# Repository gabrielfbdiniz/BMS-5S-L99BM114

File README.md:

# BMS 5S (L99BM114) — Formula ITA
### Módulo Escravo Distribuído de Sensoriamento de Células, Balanceamento e Termistores NTC (Formula SAE EV)

Repositório oficial de **Hardware** e **Documentação Técnica** do módulo escravo (Slave) do Battery Management System (BMS) da equipe **Formula ITA** (Temporada 2025-2026).

---

## Renderizações 3D do Hardware

### Módulo BMS 5S Slave (L99BM114)

Placa de 4 camadas dedicada ao monitoramento de cada bloco 5S, dotada de barreira galvânica de isolação automotiva, balanceamento passivo e filtros diferenciais de alta precisão.

<div align="center">
  
  <p><em>Vista Isométrica Superior — Destaque para o ASIC ST L99BM114, transformadores de pulso Pulse HMU2103NL (Isolated SPI Daisy-Chain), filtros de entrada e conectores Molex Micro-Fit 3.0.</em></p>
</div>

<br>

| Perspectiva Superior (Iso Top) | Perspectiva Inferior (Iso Bottom) |
| :---: | :---: |
|  |  |
| **Vista Ortográfica Superior (Top View)** | **Vista Ortográfica Inferior (Bottom View)** |
|  |  |

---

## Destaques de Arquitetura e Engenharia

1. **Topologia do Sistema no Acumulador:**
   * O acumulador total de tração é composto por **8 módulos 5s18p** em série (**40S18P = 720 células** formato 21700, 168V nominais).
   * Cada módulo possui **1x Placa BMS 5S Slave**, comunicando-se em cadeia (daisy-chain) com o BMS Master.
2. **ASIC Automotivo de Alta Resolução (ST L99BM114):**
   * Medição síncrona de tensão de células com ADC de 16 bits ($\pm 1{,}5\text{ mV}$).
   * Balanceamento passivo programável por PWM individual com resistores de potência no layer inferior.
3. **Sensoriamento Térmico Abrangente (FSAE EV4.4):**
   * Interface multiplexada para leitura de termistores NTC 10k 1% por módulo, atendendo aos requisitos de amostragem térmica de células do regulamento FSAE.
4. **Proteção Intrínseca e Filtragem EMI (FSAE EV4.4):**
   * Linhas de medição de tensão protegidas por resistores limitadores de corrente série (`R8, R11, R12, R15, R16` de 100 $\Omega$, 0805) e Ferrite Beads `TDK MMZ2012S102AT000` (1 k$\Omega$ @ 100 MHz, 0805), limitando correntes de curto-circuito em conformidade com o regulamento e atenuando transientes EMI do inversor trifásico.
   * Diodo TVS automotivo `SMA6T68AY` e capacitores cerâmicos de desacoplamento ESD (100 nF / 100 V X7R) em todas as entradas de sensoriamento.
5. **Comunicação Segura em Daisy-Chain (FSAE EV4.8 / IEC 60664):**
   * Barramento Iso-SPI diferencial serial acoplado via transformadores `Pulse HMU2103NL` ($\ge 2500\text{ V}_{RMS}$, creepage $\ge 4{,}0\text{ mm}$ e folga no layout $\ge 6{,}5\text{ mm}$).

---

## Mapeamento de Pinos do Conector de Sensoriamento (J3)

O conector **J3** (Molex Micro-Fit 3.0 de 16 vias — `43045-1600`) é a interface primária do BMS Slave para leitura das tensões de célula, linhas Kelvin de corrente e termistores NTC multiplexados:

| Pino J3 | Sinal | Descrição Técnica |
|:---:|:---:|:---|
| **1** | `BATT14` | Tensão Célula 5 (Topo do módulo, até 21.0V) — Mapeado em Cell 14 do L99BM114 |
| **2** | `BATT13` | Tensão Célula 4 (Até 16.8V) — Mapeado em Cell 13 do L99BM114 |
| **3** | `BATT12` | Tensão Célula 3 (Até 12.6V) — Mapeado em Cell 12 do L99BM114 |
| **4** | `BATT2`  | Tensão Célula 2 (Até 8.4V) — Mapeado em Cell 2 do L99BM114 |
| **5** | `BATT1`  | Tensão Célula 1 (Até 4.2V) — Mapeado em Cell 1 do L99BM114 |
| **6** | `GND_ESD`| Retorno / Referência Negativa do Módulo (0V local) |
| **7** | `ISENSEM_conn` | Entrada Kelvin negativa de sensoriamento de corrente (remoto) |
| **8** | `ISENSEP_conn` | Entrada Kelvin positiva de sensoriamento de corrente (remoto) |
| **9** | `MUX_S2` | Linha de controle digital: Bit 2 dos multiplexadores de NTC |
| **10**| `MUX_S1` | Linha de controle digital: Bit 1 dos multiplexadores de NTC |
| **11**| `MUX_S0` | Linha de controle digital: Bit 0 dos multiplexadores de NTC |
| **12**| `AGND`   | Referência analógica de sensoriamento NTC |
| **13**| `NTC_CH4`| Canal analógico multiplexado 4 (NTCs 25 a 32) |
| **14**| `NTC_CH3`| Canal analógico multiplexado 3 (NTCs 17 a 24) |
| **15**| `NTC_CH2`| Canal analógico multiplexado 2 (NTCs 9 a 16) |
| **16**| `NTC_CH1`| Canal analógico multiplexado 1 (NTCs 1 a 8) |

---

## Topologia de Células, Balanceamento e Componentes DNP (Do Not Populate)

### Topologia 5S no L99BM114
O L99BM114 é um AFE automotivo configurável de 4 a 14 células em série. Conforme a Seção 6.8 do datasheet da STMicroelectronics, as células externas (`Cell 1, 2, 13 e 14`) são mandatórias. Na topologia 5S deste projeto:
- **Células Ativas Monitoradas e Balanceadas:** `Cell 1`, `Cell 2`, `Cell 12`, `Cell 13` e `Cell 14`.
- **Células Não Utilizadas (Cell 3 a 11):** Os pinos de entrada analógica correspondentes estão interligados internamente ao barramento `/NC2` (pinos 32 a 50) e acoplados a `B2_1` através do resistor `R5 (1 kΩ)`, garantindo estabilidade do conversor ADC e impedindo nós flutuantes.

### Tabela de Componentes DNP (NÃO MONTAR)
Os seguintes componentes estão definidos formalmente como **DNP** na montagem:
| Componente | Função Original | Motivo do DNP no Módulo Slave |
| :---: | :---: | :--- |
| **`R17`** (39 $\Omega$, 2010) | Balanceamento de Cell 11 (`S11`) | Canal de célula inexistente na topologia 5S. Não montar para evitar polarização indevida do barramento `/NC2`. |
| **`R26, R27`** (100 $\Omega$, 2512) | Filtro de medição de corrente | O shunt de corrente central de 500A está alocado no módulo Master. Entradas `CURR_P` e `CURR_M` aterradas em `AGND`. |
| **`C23, C24, C25, C26, C27`** | Capacitores de filtro de corrente | DNP conjunto com o bloco de sensoriamento de corrente. |
| **`R49, R50`** (0 $\Omega$, 0805) | Seleção de referência de corrente | DNP conjunto com o bloco de corrente. |

---

## Diretrizes de Montagem e Soldagem SMT (Assembly Guidelines)

1. **Dissipação Térmica do Pad Exposto (IC1 - L99BM114-TR):**
   - O CI L99BM114 possui um Pad Térmico Exposto central (Pad 65, 5.305 x 5.305 mm) conectado a uma **matriz 3x3 de vias térmicas (diâmetro 0.30 mm, anel 0.60 mm)** interligando as camadas `F.Cu`, `In1.Cu`, `In2.Cu` e `B.Cu` ao plano `AGND`.
   - **Stencil do Pad Térmico:** Utilizar abertura de stencil fragmentada (janelada / *windowed array* de 4 ou 9 janelas) com cobertura de solda de **60% a 70%** da área do pad. Isso evita a formação de vazios gasosos (*voids*) e impede que a pasta de solda escorra excessivamente pelos furos das vias térmicas durante o refluxo.
2. **Perfil de Refluxo (Reflow Profile):**
   - Liga de solda recomendada: **SAC305 (Sn96.5 / Ag3.0 / Cu0.5)** Lead-Free, pasta Tipo 4 ou Tipo 5 (No-Clean).
   - Temperatura de pré-aquecimento: 150 °C a 200 °C (tempo de imersão: 60 a 90 segundos).
   - Temperatura de pico (*Peak Reflow*): **245 °C a 250 °C** (tempo acima do líquidus de 217 °C: 45 a 60 segundos).
3. **Inspeção Pós-Montagem:**
   - Inspecionar visualmente e com microscópio ou Raio-X o alinhamento dos pinos de 0.5 mm de pitch do L99BM114, certificando a ausência de pontes de solda (*solder bridges*) entre pinos adjacentes.
   - Verificar a continuidade e isolação da barreira galvânica de 6.5 mm com megômetro (500 VDC, resistência de isolação $> 100\text{ M}\Omega$).

---

## Estrutura do Repositório

```text
BMS 5S - STM - V2/
├── .gitignore                         # Regras de exclusão Git (KiCad, builds, temporários)
├── README.md                          # Visão geral, especificações e documentação rápida
├── LICENSE                            # Licença de Hardware Aberto (CERN-OHL-S v2)
├── CONTRIBUTING.md                     # Diretrizes de contribuição e engenharia
│
├── docs/                              # Documentação técnica e manuais
│   ├── schematics/                    # Esquemáticos oficiais em PDF vetorial
│   │   └── BMS_5S_Slave_Schematic.pdf # Esquemático hierárquico do BMS Slave V2 (KiCad 10)
│   ├── datasheets/                    # Folhas de dados de componentes críticos (L99BM114)
│   └── MANUAL_OPERACIONAL_E_MONTAGEM_BMS.md # Manual de montagem e testes
│
├── hardware/                          # Projetos de Hardware no KiCad 10
│   └── bms_5s_slave/                  # Projeto KiCad do Módulo BMS 5S Slave
│       ├── BMS_5S_v2.kicad_pro        # Projeto mestre KiCad
│       ├── BMS_5S_v2.kicad_sch        # Esquemático mestre
│       ├── BMS_5S_v2.kicad_pcb        # Layout de 4 camadas (Top/In1/In2/Bot)
│       ├── Cell_Sensing.kicad_sch     # Folha: Sensoriamento e balanceamento de células
│       ├── Current_Sensing.kicad_sch  # Folha: Entradas de derivação Kelvin para corrente
│       ├── Isolated_Communication.kicad_sch # Folha: Barreira Iso-SPI e transformadores
│       ├── NTC_and_GPIO.kicad_sch     # Folha: Condicionamento de termistores e GPIOs
│       ├── Power_Management.kicad_sch # Folha: Aterramento inteligente e alimentação
│       ├── Support_and_Debug.kicad_sch# Folha: Pontos de teste e LEDs de status
│       ├── fp-lib-table, sym-lib-table# Mapeamento local de bibliotecas
│       ├── libraries/                 # Símbolos locais e footprints dos componentes dedicados
│       ├── 3dmodels/                  # Modelos 3D STEP/WRL dos conectores e CIs
│       └── fabrication/               # Pacote de manufatura e montagem SMT
│           ├── gerbers/               # Arquivos Gerber RS-274X, Drills Excellon e ZIP final
│           ├── bom/                   # Listas de materiais (BOM CSV, Mouser, Interactive BOM)
│           └── cpl/                   # Arquivo de coordenadas Pick & Place (pos.csv)
│
└── renders/                           # Renderizações fotorrealistas em alta resolução (KiCad 10)
    ├── slave_render_iso_top.png
    ├── slave_render_iso_bottom.png
    ├── slave_render_top.png
    └── slave_render_bottom.png
```

---

## Como Abrir e Visualizar o Projeto no KiCad 10

1. **BMS 5S Slave:**
   - Abra o **KiCad 10** e carregue o arquivo de projeto:  
     `hardware/bms_5s_slave/BMS_5S_v2.kicad_pro`.
   - Abra o PCB Editor e pressione <kbd>Alt</kbd> + <kbd>3</kbd> para abrir o visualizador 3D com raytracing.
2. **Esquemático Rápido em PDF:**
   - Consulte diretamente [`docs/schematics/BMS_5S_Slave_Schematic.pdf`](docs/schematics/BMS_5S_Slave_Schematic.pdf) sem necessidade de abrir o KiCad.

---

<div align="center">
  <sub>Formula ITA — Equipe de Formula SAE Elétrico do Instituto Tecnológico de Aeronáutica (ITA).</sub>
</div>

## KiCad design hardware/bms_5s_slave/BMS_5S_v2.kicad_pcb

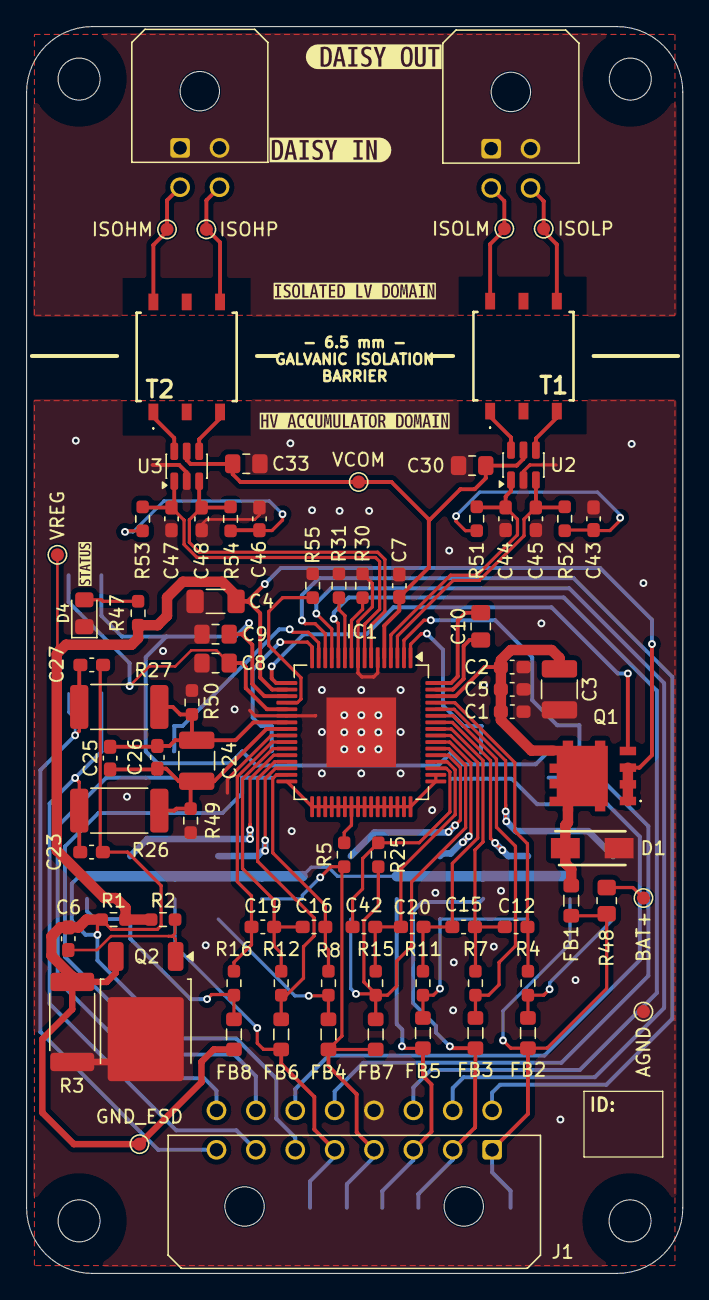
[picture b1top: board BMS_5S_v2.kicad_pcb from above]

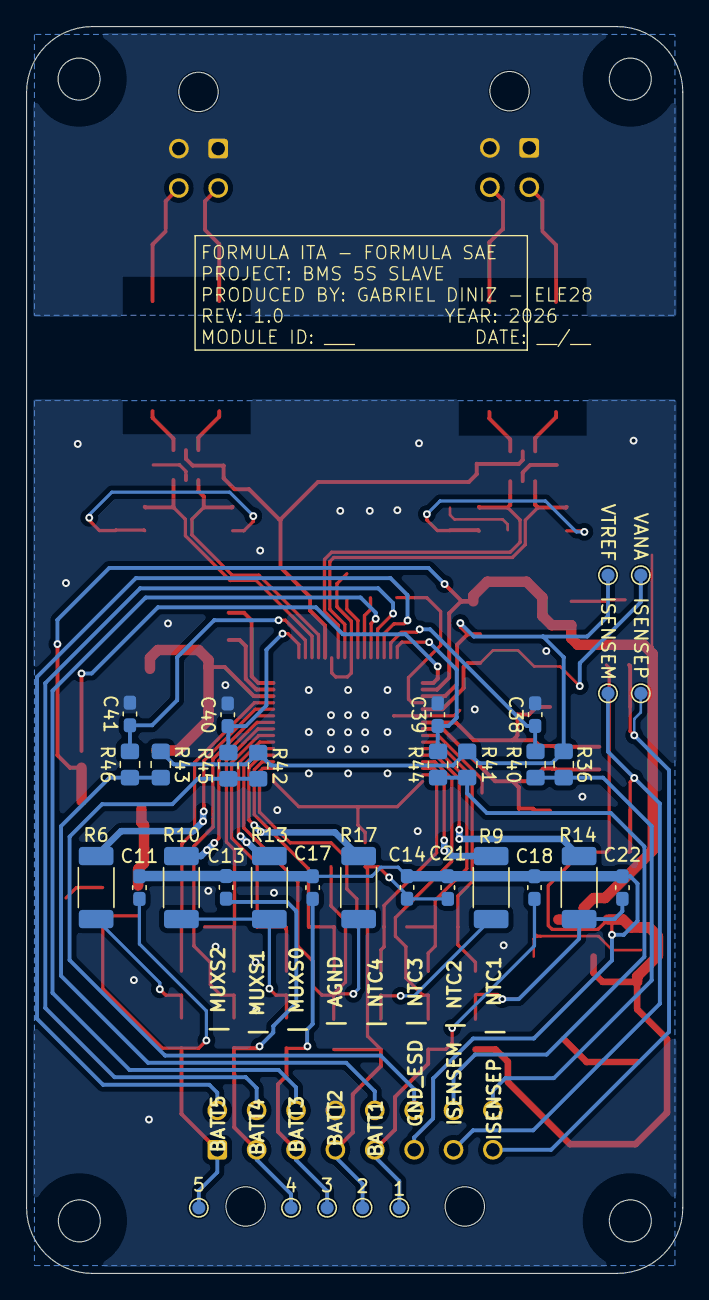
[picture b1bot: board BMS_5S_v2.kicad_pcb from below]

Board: 4 copper layers, 50.0 x 95.0 mm, 126 parts (34 on the bottom side), 73 nets.

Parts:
1: TP_C1; TestPoint_Pad_D1.0mm
2: TP_C2; TestPoint_Pad_D1.0mm
3: TP_C12; TestPoint_Pad_D1.0mm
4: TP_C13; TestPoint_Pad_D1.0mm
5: TP_C14; TestPoint_Pad_D1.0mm
AGND: TP_AGND; TestPoint_Pad_D1.0mm
BAT+: TP_VBATT; TestPoint_Pad_D1.0mm
C1: 100pF/100V; C_0603_1608Metric_Pad1.08x0.95mm_HandSolder
C2: 33nF/100V; C_0603_1608Metric_Pad1.08x0.95mm_HandSolder
C3: 2u2F/100V; C_1210_3225Metric_Pad1.33x2.70mm_HandSolder
C4: 4u7F/16V; C_1206_3216Metric_Pad1.33x1.80mm_HandSolder
C5: 100nF/100V; C_0603_1608Metric_Pad1.08x0.95mm_HandSolder
C6: 4.7nF; C_0603_1608Metric_Pad1.08x0.95mm_HandSolder
C7: 220nF/16V; C_0603_1608Metric_Pad1.08x0.95mm_HandSolder
C8: 2u2F/6.3V; C_0805_2012Metric_Pad1.18x1.45mm_HandSolder
C9: 2u2F/16V; C_0805_2012Metric_Pad1.18x1.45mm_HandSolder
C10: 1uF/16V; C_0805_2012Metric_Pad1.18x1.45mm_HandSolder
C11, C13, C14, C17, C18, C21, C22: 47nF/100V; C_0603_1608Metric_Pad1.08x0.95mm_HandSolder
C12, C15, C16, C19, C20, C42: 10nF/50V; C_0603_1608Metric_Pad1.08x0.95mm_HandSolder
C23, C27: 47nF@100V; C_0603_1608Metric_Pad1.08x0.95mm_HandSolder
C24: 10uF@10V; C_1210_3225Metric_Pad1.33x2.70mm_HandSolder
C25: 68nF@10V; C_0603_1608Metric_Pad1.08x0.95mm_HandSolder
C26: 33pF@10V; C_0603_1608Metric_Pad1.08x0.95mm_HandSolder
C30, C33: 1uF; C_0805_2012Metric_Pad1.18x1.45mm_HandSolder
C38, C39, C40, C41: 100nF; C_0603_1608Metric_Pad1.08x0.95mm_HandSolder
C43, C46: 10nF; C_0603_1608Metric_Pad1.08x0.95mm_HandSolder
C44, C45, C47, C48: 22pF; C_0603_1608Metric_Pad1.08x0.95mm_HandSolder
D1: SMA6T68AY; DIOM5126X265N
D4: 3.2V; LED_0805_2012Metric_Pad1.15x1.40mm_HandSolder
FB1, FB2, FB3, FB4, FB5, FB6, FB7, FB8: 1k@100MHz; L_0805_2012Metric_Pad1.05x1.20mm_HandSolder
GND_ESD: TP_GND_ESD; TestPoint_Pad_D1.0mm
H1, H2, H3, H4: MountingHole; MountingHole_3.2mm_M3_DIN965
IC1: L99BM114-TR; TQFP-64-1EP_10x10mm_P0.5mm_EP5.305x5.305mm
ISENSEM: TP_ISENSEM; TestPoint_Pad_D1.0mm
ISENSEP: TP_ISENSEP; TestPoint_Pad_D1.0mm
ISOHM: TP_ISOHM; TestPoint_Pad_D1.0mm
ISOHP: TP_ISOHP; TestPoint_Pad_D1.0mm
ISOLM: TP_ISOLM; TestPoint_Pad_D1.0mm
ISOLP: TP_ISOLP; TestPoint_Pad_D1.0mm
J1: Conector; Molex_Micro-Fit_3.0_43045-1600_2x08_P3.00mm_Horizontal
J4, J5: Conn_02x02_Counter_Clockwise; Molex_Micro-Fit_3.0_43045-0400_2x02_P3.00mm_Horizontal
Q1: STL8N10LF3
Q2: Q_NMOS_GDS; TO-252-2
R1, R31: 100k; R_0603_1608Metric_Pad0.98x0.95mm_HandSolder
R2, R5: 1k; R_0603_1608Metric_Pad0.98x0.95mm_HandSolder
R3: 47; R_2512_6332Metric_Pad1.40x3.35mm_HandSolder
R4, R7, R8, R11, R12, R15, R16, R25: 100@1/16W; R_0603_1608Metric_Pad0.98x0.95mm_HandSolder
R6, R9, R10, R13, R14, R17: 39@3/4W; R_2010_5025Metric_Pad1.40x2.65mm_HandSolder
R26, R27: 100@1W; R_2512_6332Metric_Pad1.40x3.35mm_HandSolder
R30, R55: 10k; R_0603_1608Metric_Pad0.98x0.95mm_HandSolder
R36, R41, R42, R43: 33k; R_0805_2012Metric_Pad1.20x1.40mm_HandSolder
R40, R44, R45, R46: 3k9; R_0805_2012Metric_Pad1.20x1.40mm_HandSolder
R47: 2k2; R_0603_1608Metric_Pad0.98x0.95mm_HandSolder
R48: 10k; R_0805_2012Metric_Pad1.20x1.40mm_HandSolder
R49, R50: 0R; R_0603_1608Metric_Pad0.98x0.95mm_HandSolder
R51, R52, R53, R54: 60.4; R_0603_1608Metric_Pad0.98x0.95mm_HandSolder
T1, T2: HMU2103NL
U2, U3: USBLC6-2SC6; SOT-23-6
VANA: TP_VANA; TestPoint_Pad_D1.0mm
VCOM: TP_VCOM; TestPoint_Pad_D1.0mm
VREG: TP_VREG; TestPoint_Pad_D1.0mm
VTREF: TP_VTREF; TestPoint_Pad_D1.0mm
kibuzzard-6AD93452: G***; kibuzzard-6AD93452
kibuzzard-6AD93460: G***; kibuzzard-6AD93460
kibuzzard-6ADA909C: G***; kibuzzard-6ADA909C
kibuzzard-6ADA916E: G***; kibuzzard-6ADA916E
kibuzzard-6ADA9153: G***; kibuzzard-6ADA9153

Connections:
/B2_1: FB6.1, IC1.29 (B2_1), R12.2
/B12_11: FB7.1, IC1.54 (B12_11), R15.2, R17.2, R25.2
/B14_13: FB3.1, IC1.59 (B14_13), R7.2
/C0: C19.2, IC1.26 (C0), R16.1
/C1: C16.2, C19.1, IC1.27 (C1), R12.1
/C2: C16.1, IC1.31 (C2), R8.1
/C10: C42.2, IC1.51 (C10), R25.1
/C11: C20.2, C42.1, IC1.52 (C11), R15.1
/C12: C15.2, C20.1, IC1.56 (C12), R11.1
/C13: C12.2, C15.1, IC1.57 (C13), R7.1
/C14: C12.1, IC1.61 (C14), R4.1
/CAP1: C10.1, IC1.64 (CAP1)
/CAP2: C10.2, IC1.63 (CAP2)
/EXTDRV: IC1.17 (EXTDRV), Q1.4 (G)
/FAULTH: IC1.10 (GPIO1__FAULTH), R30.1
/FAULTL: IC1.11 (GPIO2__FAULTL), R31.1
/GPIO6: C38.1, IC1.15 (GPIO6), R40.1
/GPIO7: C39.1, IC1.16 (GPIO7__WAKEUP), R44.1
/GPIO8: C40.1, IC1.1 (GPIO8__SCK), R45.1
/GPIO9: C41.1, IC1.2 (GPIO9__SDO), R46.1
/ISENSEM: C24.1, C25.1, C26.1, IC1.24 (ISENSEM), R26.1, R49.2
/ISENSEP: C24.2, C25.2, C26.2, IC1.23 (ISENSEP), R27.2, R50.1
/ISOHM: C47.1, IC1.8 (ISOHM), R53.2, U3.1 (I/O1)
/ISOHP: C48.1, IC1.7 (ISOHP), R54.1, U3.3 (I/O2)
/ISOLM: C44.1, IC1.4 (ISOLM), R51.2, U2.1 (I/O1)
/ISOLP: C45.1, IC1.3 (ISOLP), R52.1, U2.3 (I/O2)
/NC2: IC1.32 (C3), IC1.33 (S3), IC1.34 (B4_3), IC1.35 (S4), IC1.36 (C4), IC1.37 (C5), IC1.38 (S5), IC1.39 (B6_5), IC1.40 (S6), IC1.41 (C6), IC1.42 (C7), IC1.43 (S7), IC1.44 (B8_7), IC1.45 (S8), IC1.46 (C8), IC1.47 (C9), IC1.48 (S9), IC1.49 (B10_9), IC1.50 (S10), R5.2
/S1: IC1.28 (S1), R14.1
/S2: IC1.30 (S2), R9.1
/S11: IC1.53 (S11), R17.1
/S12: IC1.55 (S12), R13.1
/S13: IC1.58 (S13), R10.1
/S14: IC1.60 (S14), R6.1
/SPIEN: IC1.20 (SPIEN), R55.1
/VBAT: C1.1, C2.1, C3.1, C5.1, D1.1 (K), FB1.1, IC1.62 (VBAT), Q1.5 (D_1), Q1.6 (D_2), Q1.7 (D_3), Q1.8 (D_4), Q1.9 (D_5), Q1.10 (D_6), Q1.11 (D_7), Q1.12 (D_8), Q1.13 (D_9)
AGND: AGND.1, C1.2, C2.2, C3.2, C4.2, C5.2, C7.2, C8.2, C9.2, C30.1, C33.1, C38.2, C39.2, C40.2, C41.2, C43.2, C44.2, C45.2, C46.2, C47.2, C48.2, D1.2 (A), D4.1 (K), IC1.6 (CGND), IC1.9 (DGND), IC1.22 (AGND), IC1.25 (GNDREF), IC1.65 (GND), J1.12, Q2.2 (D), R3.1, R30.2, R31.2, R49.1, R50.2, R55.2, U2.2 (GND), U3.2 (GND)
BATT 1: 1.1, C18.1, FB6.2, J1.5
BATT 2: 2.1, C14.1, C21.1, FB4.2, FB7.2, J1.4, R5.1
BATT 12: 3.1, C17.1, FB5.2, J1.3
BATT 13: 4.1, C13.1, FB3.2, J1.2
BATT 14: 5.1, C11.1, FB1.2, FB2.2, J1.1, R48.1
BATT_PLUS: BAT+.1, R48.2
GND_ESD: C6.1, C11.2, C13.2, C14.2, C17.2, C18.2, C21.2, C22.2, C23.2, C27.2, FB8.2, GND_ESD.1, J1.6, Q2.3 (S), R1.1, R3.2
GND_EXT: J4.1, J4.2, J5.1, J5.2
ISENSEM_conn: C23.1, ISENSEM.1, J1.7, R26.2
ISENSEP_conn: C27.1, ISENSEP.1, J1.8, R27.1
ISOHM_c: ISOHM.1, J5.3, T2.6 (SEC_3)
ISOHP_c: ISOHP.1, J5.4, T2.4 (SEC_1)
ISOLM_c: ISOLM.1, J4.3, T1.6 (SEC_3)
ISOLP_c: ISOLP.1, J4.4, T1.4 (SEC_1)
MUX_S0: IC1.12 (GPIO3), J1.11
MUX_S1: IC1.13 (GPIO4), J1.10
MUX_S2: IC1.14 (GPIO5), J1.9
NTC_CH1: J1.16, R36.1, R40.2
NTC_CH2: J1.15, R41.1, R44.2
NTC_CH3: J1.14, R42.1, R45.2
NTC_CH4: J1.13, R43.1, R46.2
unnamed: C22.1, FB8.1, R14.2, R16.2
unnamed: C43.1, R51.1, R52.2
unnamed: C46.1, R53.1, R54.2
unnamed: D4.2 (A), R47.2
unnamed: FB2.1, R4.2, R6.2
unnamed: FB4.1, R8.2, R9.2
unnamed: FB5.1, R10.2, R11.2, R13.2
unnamed: C6.2, Q2.1 (G), R2.2
unnamed: T1.1 (PRI_1), U2.6 (I/O1)
unnamed: T1.3 (PRI_3), U2.4 (I/O2)
unnamed: T2.1 (PRI_1), U3.6 (I/O1)
unnamed: T2.3 (PRI_3), U3.4 (I/O2)
VANA: C8.1, IC1.21 (VANA), VANA.1
VCOM: C7.1, C30.2, C33.2, IC1.5 (VCOM), U2.5 (VBUS), U3.5 (VBUS), VCOM.1
VREG: C4.1, IC1.18 (VREG), Q1.1 (S_1), Q1.2 (S_2), Q1.3 (S_3), R1.2, R2.1, R47.1, VREG.1
VTREF: C9.1, IC1.19 (VTREF), R36.2, R41.2, R42.2, R43.2, VTREF.1

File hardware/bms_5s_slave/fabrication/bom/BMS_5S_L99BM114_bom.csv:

"Refs","Value","Footprint","Qty","DNP"
"C1","100pF/100V","Capacitor_SMD:C_0603_1608Metric_Pad1.08x0.95mm_HandSolder","1",""
"C2","33nF/100V","Capacitor_SMD:C_0603_1608Metric_Pad1.08x0.95mm_HandSolder","1",""
"C3","2u2F/100V","Capacitor_SMD:C_1210_3225Metric_Pad1.33x2.70mm_HandSolder","1",""
"C4","4u7F/16V","Capacitor_SMD:C_1206_3216Metric_Pad1.33x1.80mm_HandSolder","1",""
"C5","100nF/100V","Capacitor_SMD:C_0603_1608Metric_Pad1.08x0.95mm_HandSolder","1",""
"C6","4.7nF","Capacitor_SMD:C_0603_1608Metric_Pad1.08x0.95mm_HandSolder","1",""
"C7","220nF/16V","Capacitor_SMD:C_0603_1608Metric_Pad1.08x0.95mm_HandSolder","1",""
"C8","2u2F/6.3V","Capacitor_SMD:C_0805_2012Metric_Pad1.18x1.45mm_HandSolder","1",""
"C9","2u2F/16V","Capacitor_SMD:C_0805_2012Metric_Pad1.18x1.45mm_HandSolder","1",""
"C10","1uF/16V","Capacitor_SMD:C_0805_2012Metric_Pad1.18x1.45mm_HandSolder","1",""
"C11,C13,C14,C17,C18,C21,C22","47nF/100V","Capacitor_SMD:C_0603_1608Metric_Pad1.08x0.95mm_HandSolder","7",""
"C12,C15,C16,C19,C20,C42","10nF/50V","Capacitor_SMD:C_0603_1608Metric_Pad1.08x0.95mm_HandSolder","6",""
"C23,C27","47nF@100V","Capacitor_SMD:C_0603_1608Metric_Pad1.08x0.95mm_HandSolder","2","DNP"
"C24","10uF@10V","Capacitor_SMD:C_1210_3225Metric_Pad1.33x2.70mm_HandSolder","1","DNP"
"C25","68nF@10V","Capacitor_SMD:C_0603_1608Metric_Pad1.08x0.95mm_HandSolder","1","DNP"
"C26","33pF@10V","Capacitor_SMD:C_0603_1608Metric_Pad1.08x0.95mm_HandSolder","1","DNP"
"C30,C33","1uF","Capacitor_SMD:C_0805_2012Metric_Pad1.18x1.45mm_HandSolder","2",""
"C38-C41","100nF","Capacitor_SMD:C_0603_1608Metric_Pad1.08x0.95mm_HandSolder","4",""
"C43,C46","10nF","Capacitor_SMD:C_0603_1608Metric_Pad1.08x0.95mm_HandSolder","2",""
"C44,C45,C47,C48","22pF","Capacitor_SMD:C_0603_1608Metric_Pad1.08x0.95mm_HandSolder","4",""
"D1","SMA6T68AY","DIOM5126X265N:DIOM5126X265N","1",""
"D4","3.2V","LED_SMD:LED_0805_2012Metric_Pad1.15x1.40mm_HandSolder","1",""
"FB1-FB8","1k@100MHz","Inductor_SMD:L_0805_2012Metric_Pad1.05x1.20mm_HandSolder","8",""
"IC1","L99BM114-TR","Package_QFP:TQFP-64-1EP_10x10mm_P0.5mm_EP5.305x5.305mm","1",""
"J1","Conector","Connector_Molex:Molex_Micro-Fit_3.0_43045-1600_2x08_P3.00mm_Horizontal","1",""
"J4,J5","Conn_02x02_Counter_Clockwise","Connector_Molex:Molex_Micro-Fit_3.0_43045-0400_2x02_P3.00mm_Horizontal","2",""
"Q1","STL8N10LF3","STL8N10LF3:STL8N10LF3","1",""
"Q2","Q_NMOS_GDS","Package_TO_SOT_SMD:TO-252-2","1",""
"R1,R31","100k","Resistor_SMD:R_0603_1608Metric_Pad0.98x0.95mm_HandSolder","2",""
"R2,R5","1k","Resistor_SMD:R_0603_1608Metric_Pad0.98x0.95mm_HandSolder","2",""
"R3","47","Resistor_SMD:R_2512_6332Metric_Pad1.40x3.35mm_HandSolder","1",""
"R4,R7,R8,R11,R12,R15,R16,R25","100@1/16W","Resistor_SMD:R_0603_1608Metric_Pad0.98x0.95mm_HandSolder","8",""
"R6,R9,R10,R13,R14","39@3/4W","Resistor_SMD:R_2010_5025Metric_Pad1.40x2.65mm_HandSolder","5",""
"R17","39@3/4W","Resistor_SMD:R_2010_5025Metric_Pad1.40x2.65mm_HandSolder","1","DNP"
"R26,R27","100@1W","Resistor_SMD:R_2512_6332Metric_Pad1.40x3.35mm_HandSolder","2","DNP"
"R30,R55","10k","Resistor_SMD:R_0603_1608Metric_Pad0.98x0.95mm_HandSolder","2",""
"R36,R41-R43","33k","Resistor_SMD:R_0805_2012Metric_Pad1.20x1.40mm_HandSolder","4",""
"R40,R44-R46","3k9","Resistor_SMD:R_0805_2012Metric_Pad1.20x1.40mm_HandSolder","4",""
"R47","2k2","Resistor_SMD:R_0603_1608Metric_Pad0.98x0.95mm_HandSolder","1",""
"R48","10k","Resistor_SMD:R_0805_2012Metric_Pad1.20x1.40mm_HandSolder","1",""
"R49,R50","0R","Resistor_SMD:R_0603_1608Metric_Pad0.98x0.95mm_HandSolder","2","DNP"
"R51-R54","60.4","Resistor_SMD:R_0603_1608Metric_Pad0.98x0.95mm_HandSolder","4",""
"T1,T2","HMU2103NL","HMU2103NL:HMU2103NL","2",""
"U2,U3","USBLC6-2SC6","Package_TO_SOT_SMD:SOT-23-6","2",""

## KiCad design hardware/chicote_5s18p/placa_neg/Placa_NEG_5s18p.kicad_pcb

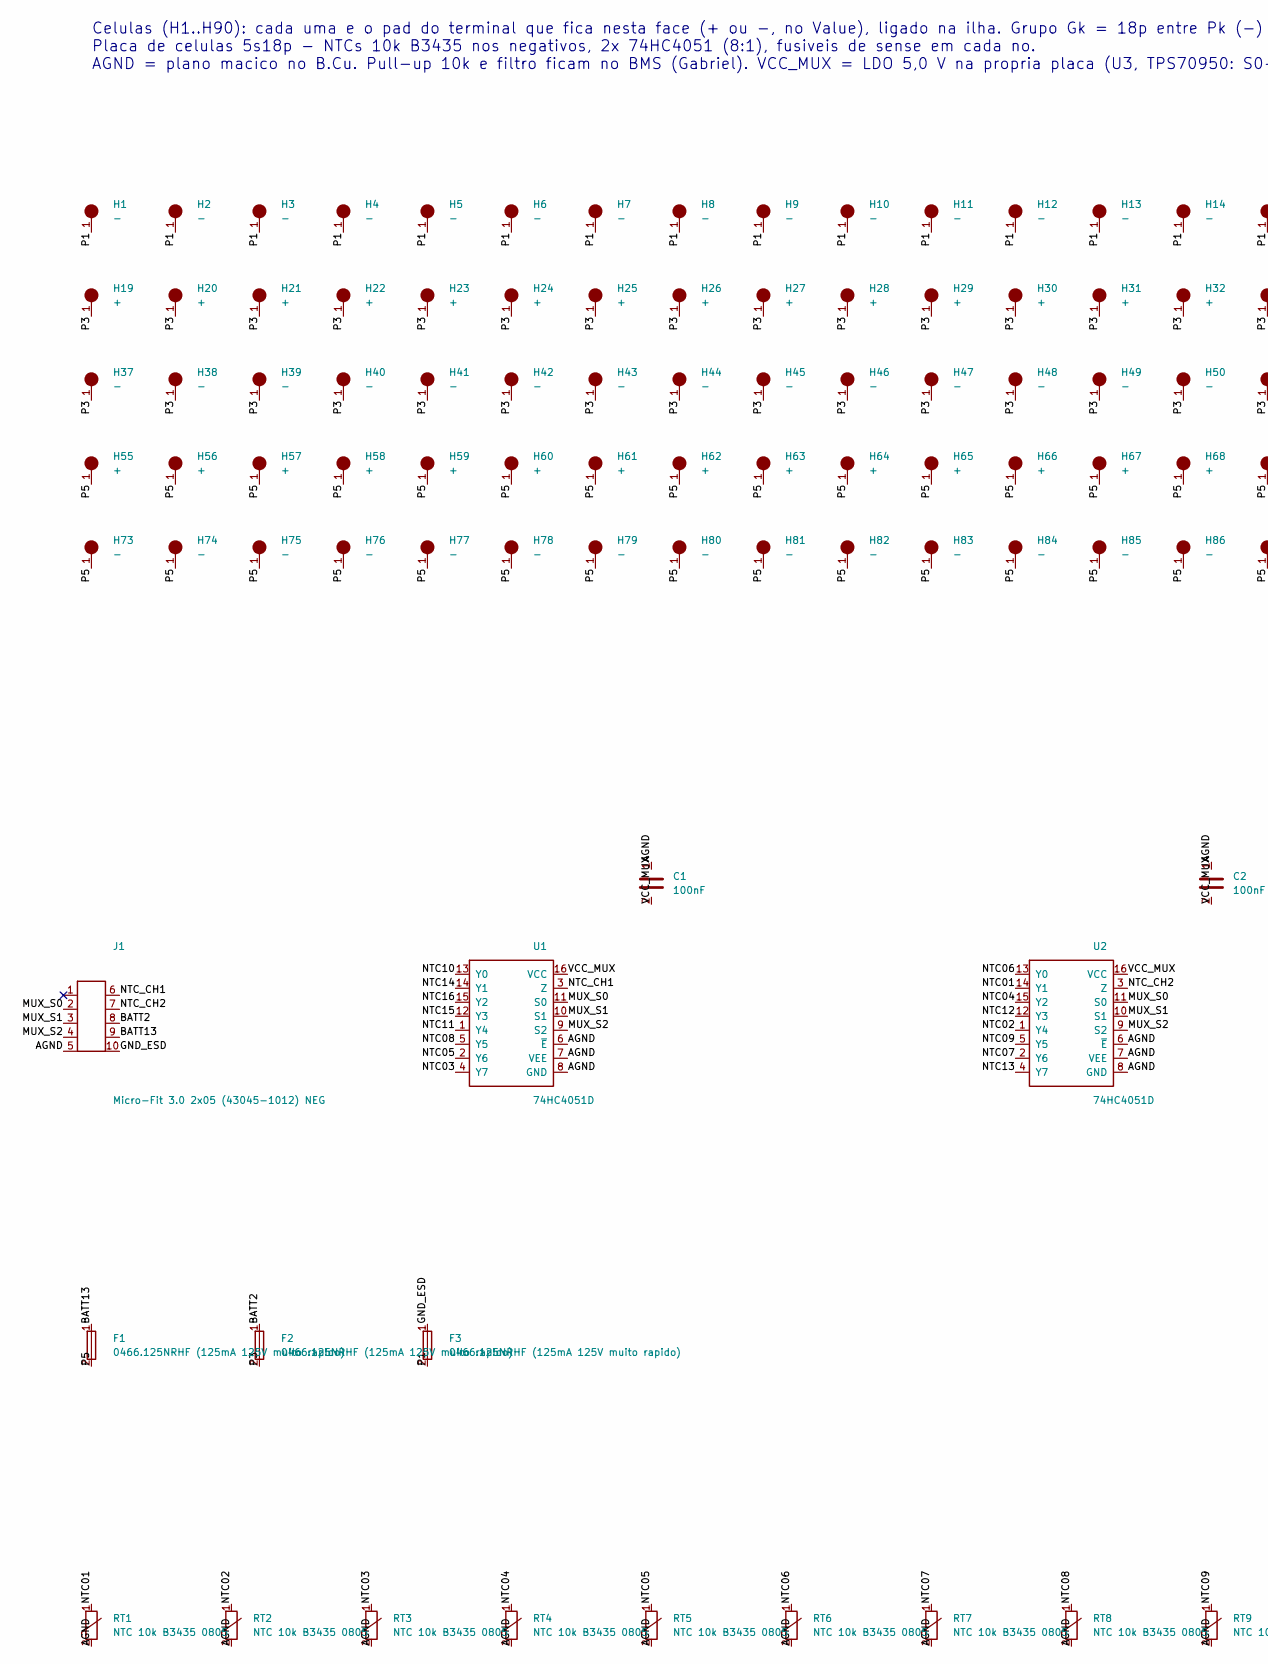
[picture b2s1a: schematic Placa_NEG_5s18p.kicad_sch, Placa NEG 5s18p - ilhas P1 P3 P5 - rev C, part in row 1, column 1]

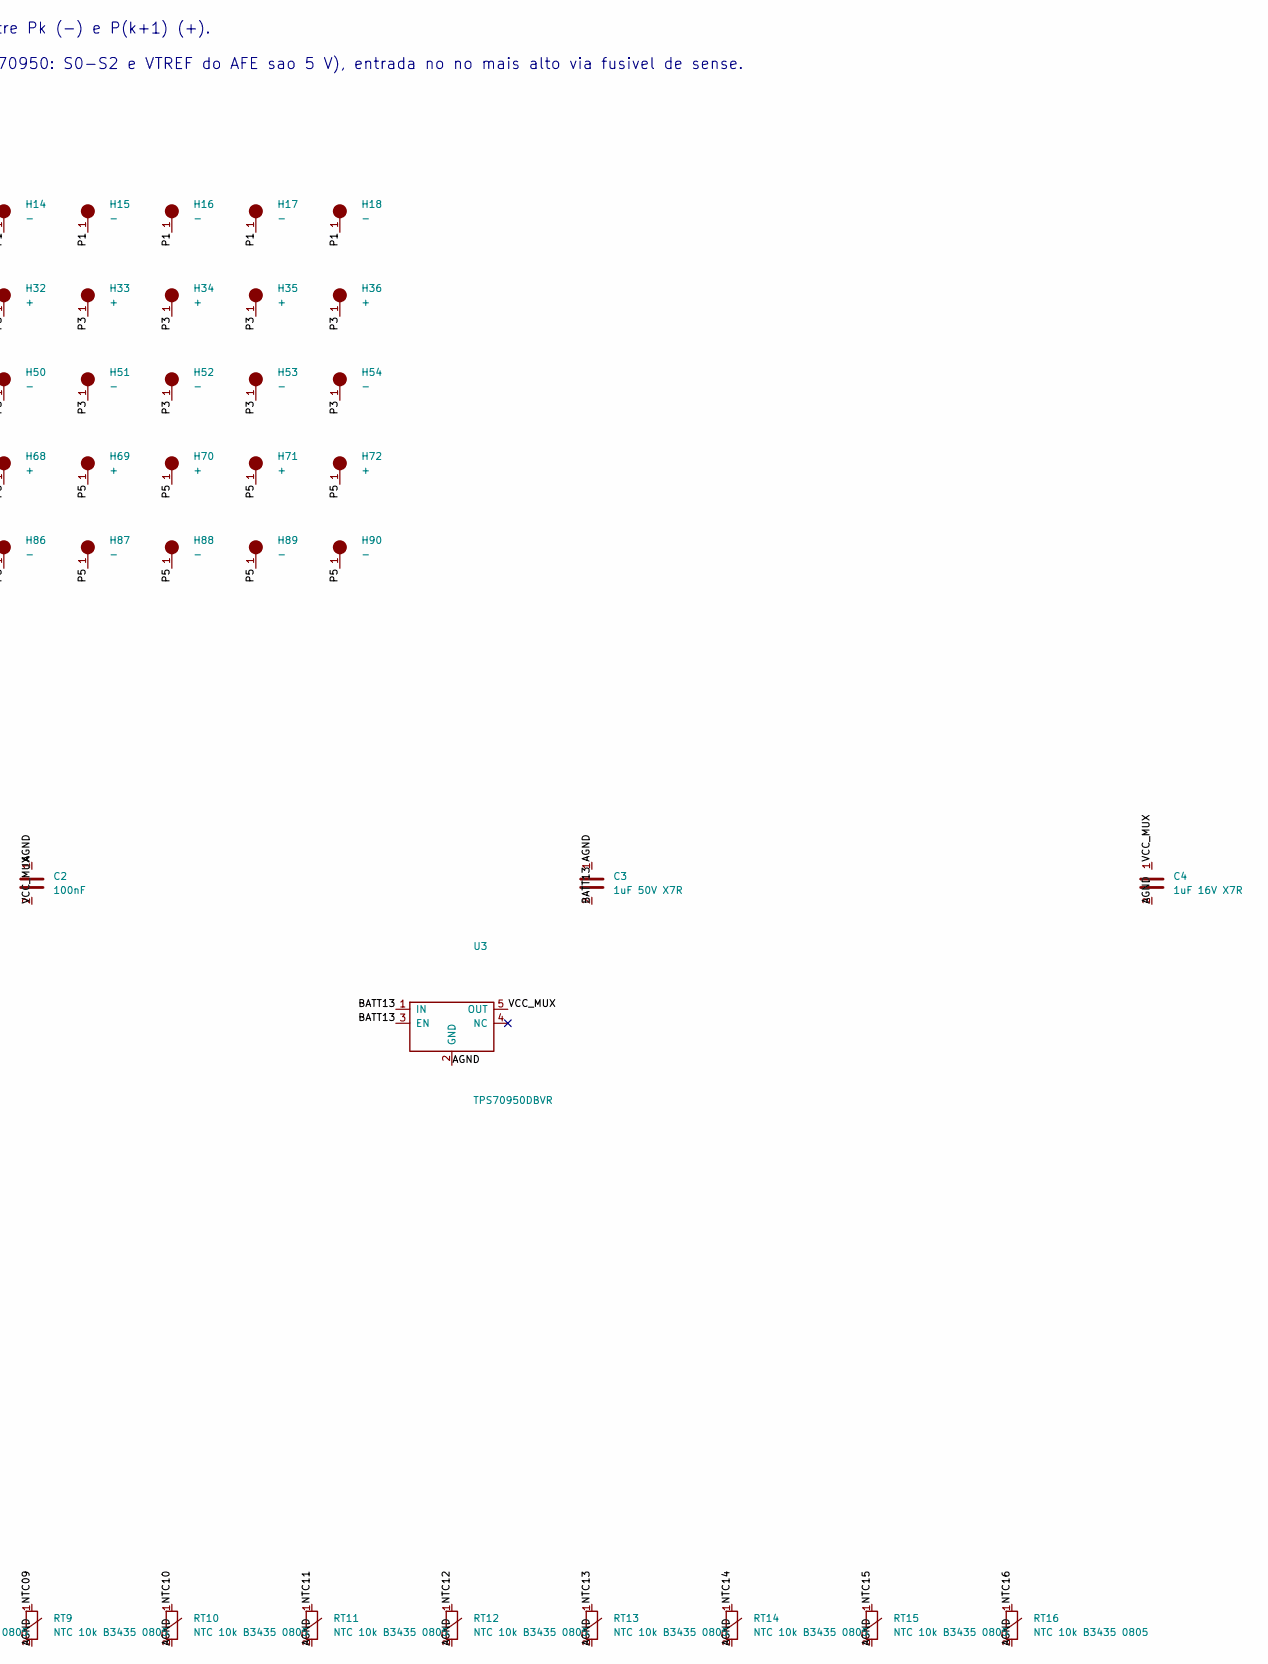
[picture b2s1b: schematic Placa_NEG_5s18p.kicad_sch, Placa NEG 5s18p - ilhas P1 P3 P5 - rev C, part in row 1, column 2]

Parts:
C1, C2: 100nF; C_0805_2012Metric
C3: 1uF 50V X7R; C_0805_2012Metric
C4: 1uF 16V X7R; C_0805_2012Metric
F1, F2, F3: 0466.125NRHF (125mA 125V muito rapido); Fuse_1206_3216Metric
H1, H2, H3, H4, H5, H6, H7, H8, H9, H10, H11, H12, H13, H14, H15, H16, H17, H18, H37, H38, H39, H40, H41, H42, H43, H44, H45, H46, H47, H48, H49, H50, H51, H52, H53, H54, H73, H74, H75, H76, H77, H78, H79, H80, H81, H82, H83, H84, H85, H86, H87, H88, H89, H90: -; Celula_21700_terminal_NEG
H19, H20, H21, H22, H23, H24, H25, H26, H27, H28, H29, H30, H31, H32, H33, H34, H35, H36, H55, H56, H57, H58, H59, H60, H61, H62, H63, H64, H65, H66, H67, H68, H69, H70, H71, H72: +; Celula_21700_terminal_POS
J1: Micro-Fit 3.0 2x05 (43045-1012) NEG; Molex_Micro-Fit_3.0_43045-1012_2x05_P3.00mm_Vertical
RT1, RT2, RT3, RT4, RT5, RT6, RT7, RT8, RT9, RT10, RT11, RT12, RT13, RT14, RT15, RT16: NTC 10k B3435 0805; R_0805_2012Metric
U1, U2: 74HC4051D; SOIC-16_3.9x9.9mm_P1.27mm
U3: TPS70950DBVR; SOT-23-5

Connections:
AGND: C1.1, C2.1, C3.1, C4.2, J1.5, RT1.2, RT2.2, RT3.2, RT4.2, RT5.2, RT6.2, RT7.2, RT8.2, RT9.2, RT10.2, RT11.2, RT12.2, RT13.2, RT14.2, RT15.2, RT16.2, U1.6 (~E), U1.7 (VEE), U1.8 (GND), U2.6 (~E), U2.7 (VEE), U2.8 (GND), U3.2 (GND)
BATT2: F2.1, J1.8
BATT13: C3.2, F1.1, J1.9, U3.1 (IN), U3.3 (EN)
GND_ESD: F3.1, J1.10
MUX_S0: J1.2, U1.11 (S0), U2.11 (S0)
MUX_S1: J1.3, U1.10 (S1), U2.10 (S1)
MUX_S2: J1.4, U1.9 (S2), U2.9 (S2)
NTC01: RT1.1, U2.14 (Y1)
NTC02: RT2.1, U2.1 (Y4)
NTC03: RT3.1, U1.4 (Y7)
NTC04: RT4.1, U2.15 (Y2)
NTC05: RT5.1, U1.2 (Y6)
NTC06: RT6.1, U2.13 (Y0)
NTC07: RT7.1, U2.2 (Y6)
NTC08: RT8.1, U1.5 (Y5)
NTC09: RT9.1, U2.5 (Y5)
NTC10: RT10.1, U1.13 (Y0)
NTC11: RT11.1, U1.1 (Y4)
NTC12: RT12.1, U2.12 (Y3)
NTC13: RT13.1, U2.4 (Y7)
NTC14: RT14.1, U1.14 (Y1)
NTC15: RT15.1, U1.12 (Y3)
NTC16: RT16.1, U1.15 (Y2)
NTC_CH1: J1.6, U1.3 (Z)
NTC_CH2: J1.7, U2.3 (Z)
P1: F3.2, H1.1, H2.1, H3.1, H4.1, H5.1, H6.1, H7.1, H8.1, H9.1, H10.1, H11.1, H12.1, H13.1, H14.1, H15.1, H16.1, H17.1, H18.1
P3: F2.2, H19.1, H20.1, H21.1, H22.1, H23.1, H24.1, H25.1, H26.1, H27.1, H28.1, H29.1, H30.1, H31.1, H32.1, H33.1, H34.1, H35.1, H36.1, H37.1, H38.1, H39.1, H40.1, H41.1, H42.1, H43.1, H44.1, H45.1, H46.1, H47.1, H48.1, H49.1, H50.1, H51.1, H52.1, H53.1, H54.1
P5: F1.2, H55.1, H56.1, H57.1, H58.1, H59.1, H60.1, H61.1, H62.1, H63.1, H64.1, H65.1, H66.1, H67.1, H68.1, H69.1, H70.1, H71.1, H72.1, H73.1, H74.1, H75.1, H76.1, H77.1, H78.1, H79.1, H80.1, H81.1, H82.1, H83.1, H84.1, H85.1, H86.1, H87.1, H88.1, H89.1, H90.1
VCC_MUX: C1.2, C2.2, C4.1, U1.16 (VCC), U2.16 (VCC), U3.5 (OUT)

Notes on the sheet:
Celulas (H1..H90): cada uma e o pad do terminal que fica nesta face (+ ou -, no Value), ligado na ilha. Grupo Gk = 18p entre Pk (-) e P(k+1) (+). Placa de celulas 5s18p - NTCs 10k B3435 nos negativos, 2x 74HC4051 (8:1), fusiveis de sense em cada no. AGND = plano macico no B.Cu. Pull-up 10k e filtro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

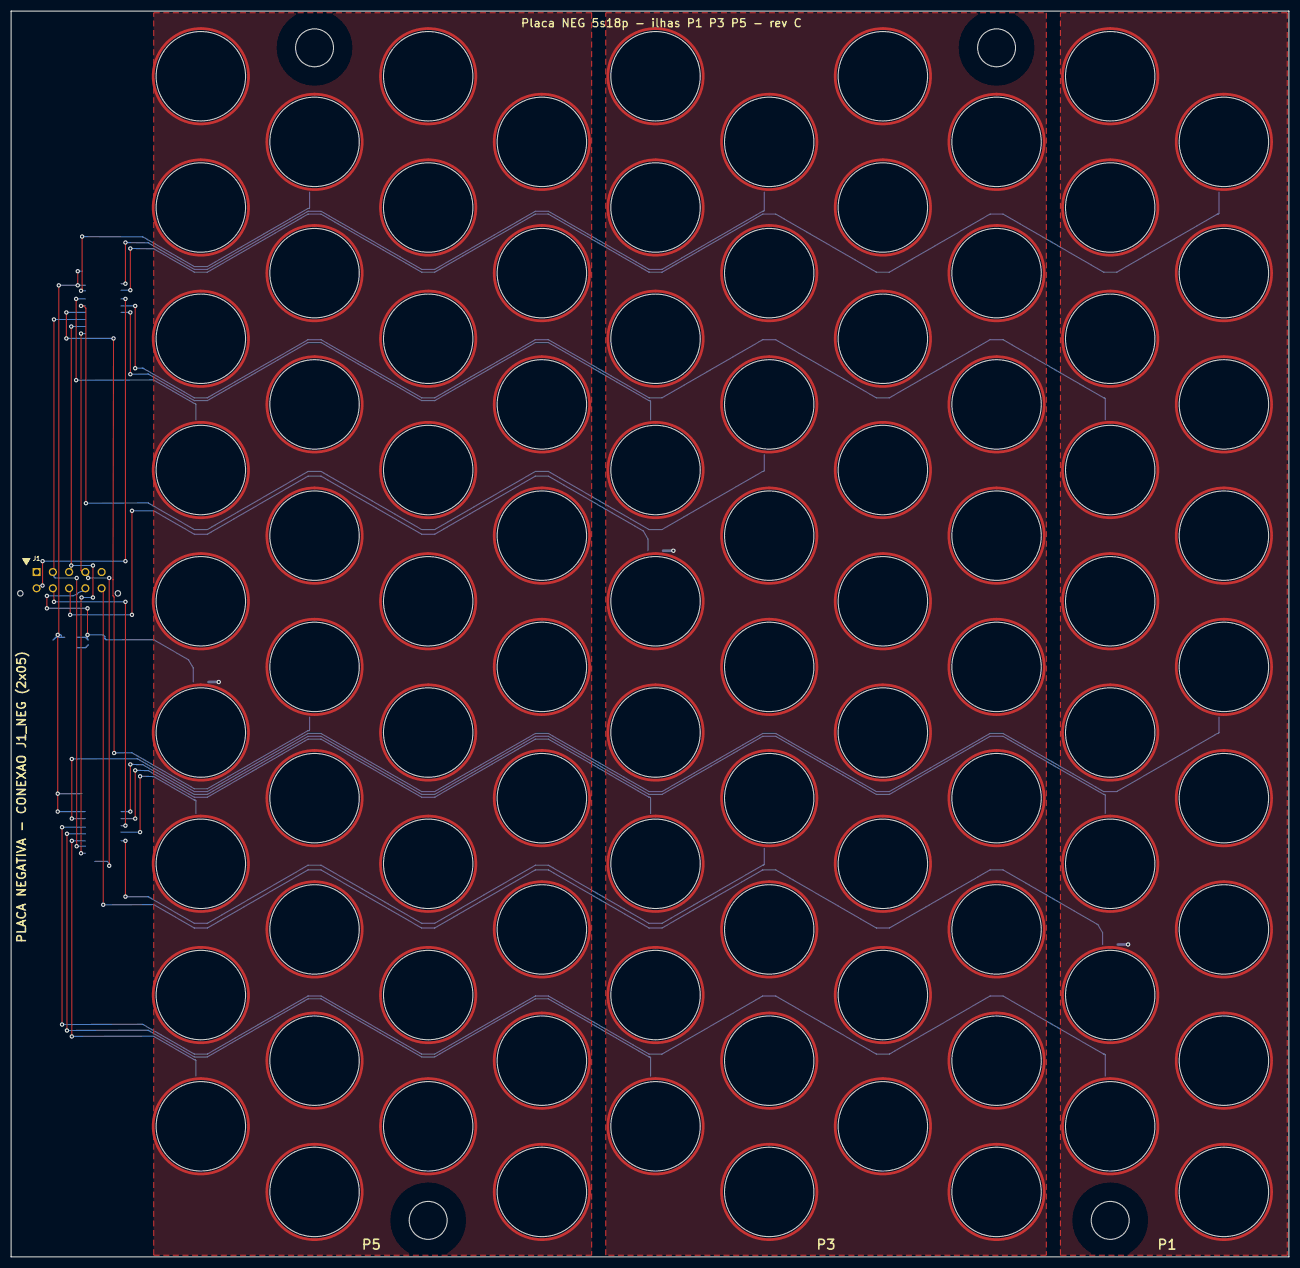
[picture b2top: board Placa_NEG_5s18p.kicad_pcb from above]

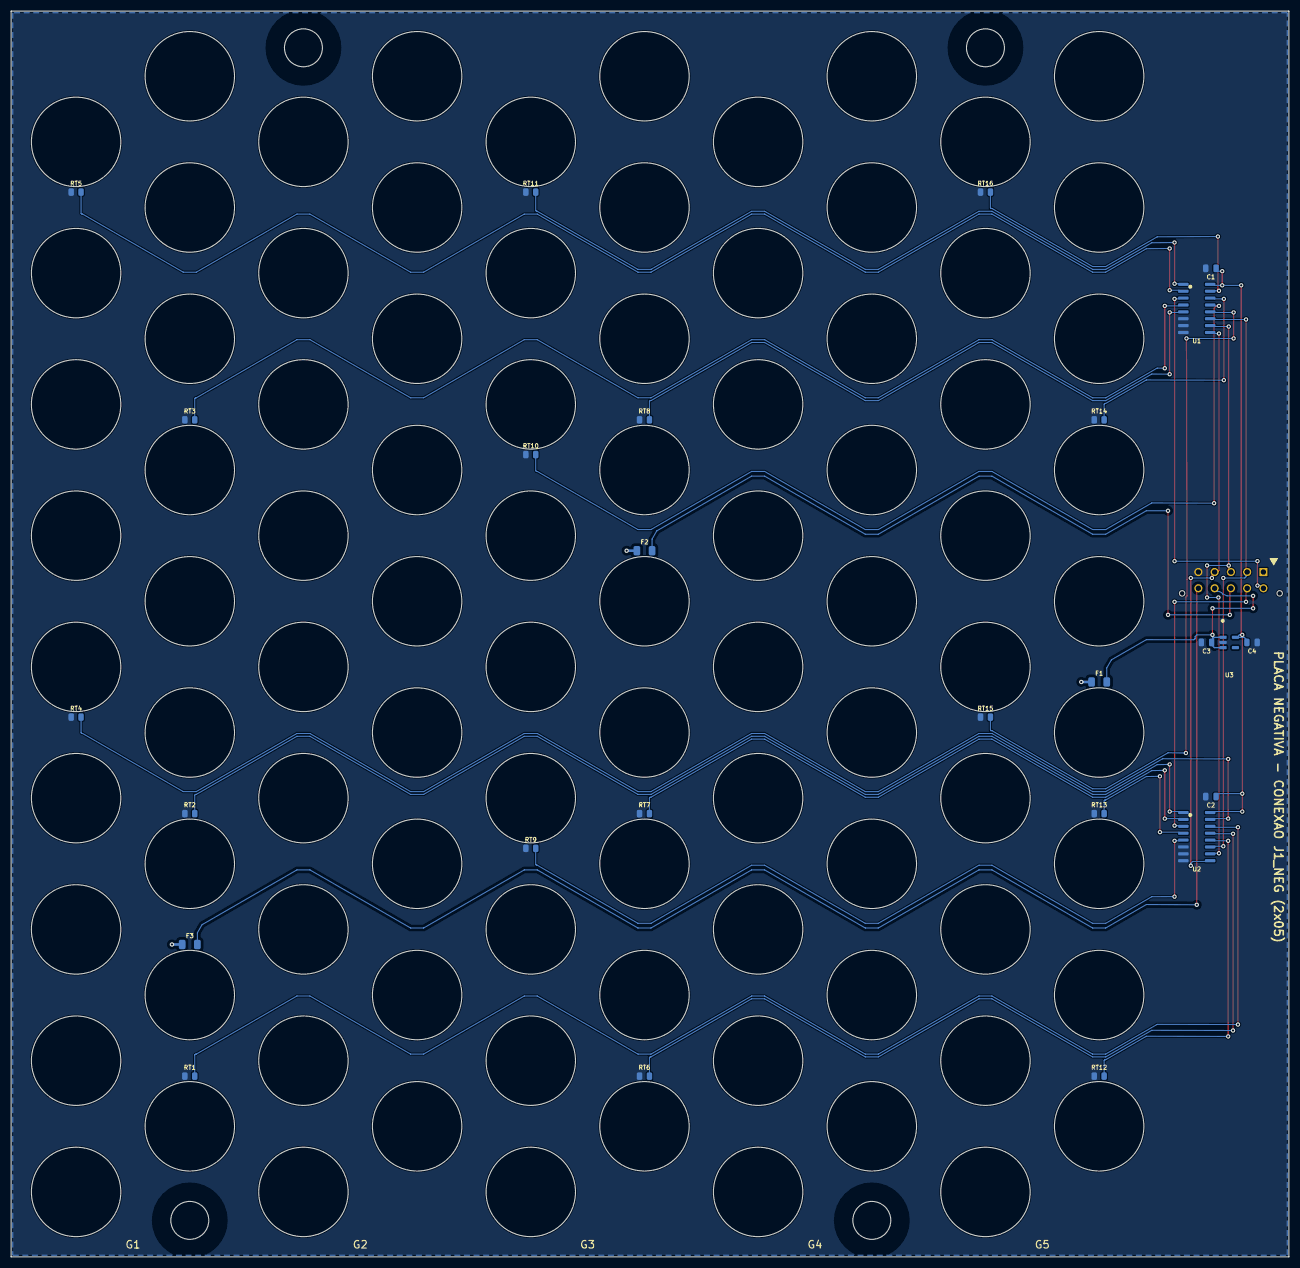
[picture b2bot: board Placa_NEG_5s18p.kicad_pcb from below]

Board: 2 copper layers, 235.8 x 229.9 mm, 121 parts (26 on the bottom side), 29 nets.

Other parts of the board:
MH1, MH2, MH3, MH4: M6; Furo_Fixacao_7mm
